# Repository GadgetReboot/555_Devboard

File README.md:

# 555_Devboard
A breakout board for the 555 timer

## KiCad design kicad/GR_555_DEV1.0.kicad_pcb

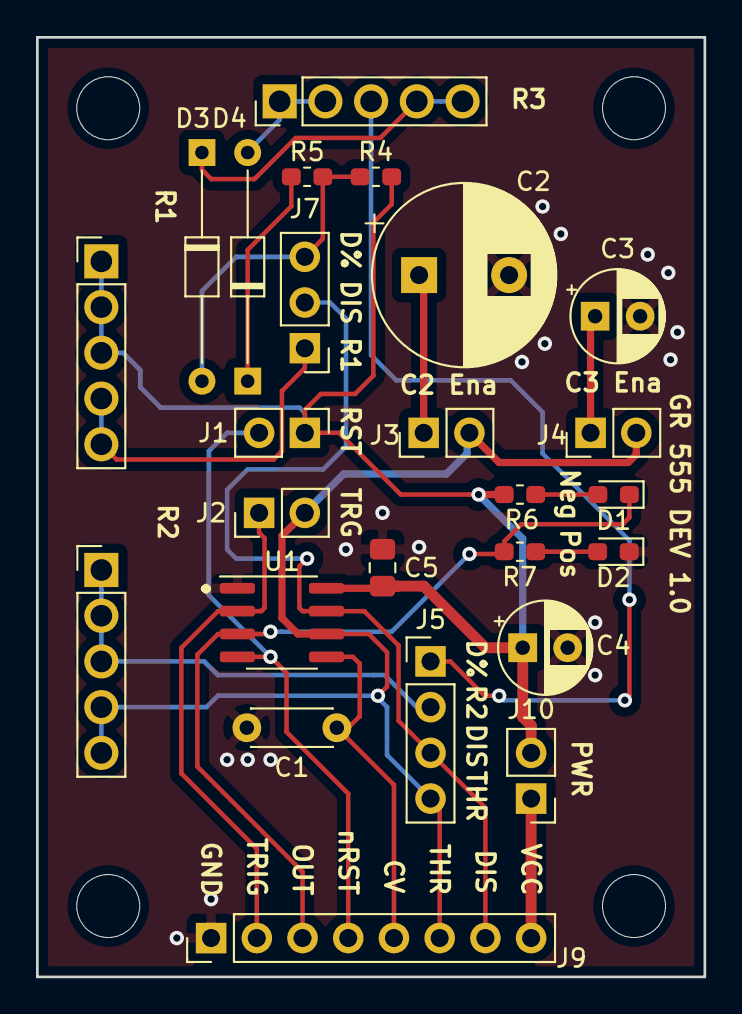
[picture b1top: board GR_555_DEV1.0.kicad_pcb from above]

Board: 2 copper layers, 37.1 x 52.2 mm, 25 parts (0 on the bottom side), 20 nets.

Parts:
C1: 1nF; C_Disc_D4.3mm_W1.9mm_P5.00mm
C2: 1uF; CP_Radial_D10.0mm_P5.00mm
C3: 10nF; CP_Radial_D5.0mm_P2.50mm
C4: 1uF; CP_Radial_D5.0mm_P2.50mm
C5: 100nF; C_0805_2012Metric_Pad1.15x1.40mm_HandSolder
D1: RED; LED_0603_1608Metric_Pad1.05x0.95mm_HandSolder
D2: GREEN; LED_0603_1608Metric_Pad1.05x0.95mm_HandSolder
D3, D4: D_ALT; D_DO-34_SOD68_P12.70mm_Horizontal
J1, J2, J3, J4, J10: 1x2; PinHeader_1x02_P2.54mm_Vertical
J5: 1x3; PinHeader_1x04_P2.54mm_Vertical
J6, J8, J11: 1x5; PinHeader_1x05_P2.54mm_D0472_Vertical
J7: 1x3; PinHeader_1x03_P2.54mm_Vertical
J9: 1x8; PinHeader_1x08_P2.54mm_Vertical
R4, R5: 4.7K; R_0603_1608Metric_Pad1.05x0.95mm_HandSolder
R6, R7: 680; R_0603_1608Metric_Pad1.05x0.95mm_HandSolder
U1: LM555; SOIC-8_3.9x4.9mm_P1.27mm

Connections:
/CV: C1.1, J9.5, U1.5
/DIS: J5.3, J7.2, J9.7, U1.7
/OUT: D1.1, J9.3, R7.1, U1.3
/RST: J1.2, J9.4, U1.4
/THR: J2.2, J3.2, J4.2, J5.4, J6.4, J6.5, J9.6, U1.6
/TRIG: J2.1, J9.2, U1.2
GND: C1.2, C2.2, C3.2, C4.2, C5.2, D2.1, J9.1, U1.1
unnamed: C2.1, J3.1
unnamed: C3.1, J4.1
unnamed: D1.2, R6.2
unnamed: D2.2, R7.2
unnamed: D3.1, J11.4, J11.5
unnamed: D3.2, J7.3, R4.2, R5.1
unnamed: D4.1, R5.2
unnamed: D4.2, J11.1, J11.2
unnamed: J5.2, J6.1, J6.2, J6.3
unnamed: J7.1, J8.4, J8.5
unnamed: J9.8, J10.1
unnamed: J5.1, J11.3
VCC: C4.1, C5.1, J1.1, J8.1, J8.2, J8.3, J10.2, R4.1, R6.1, U1.8

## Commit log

2019-07-03 KiCad Files
